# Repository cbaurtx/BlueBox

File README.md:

# BlueBox

BlueBox is a Bluetooth adapter for the RetroBox using an ESP32 system on a chip (ESP32-Wrover).

Refer to the file LICENSE.md for licenses (hardware and software).  

It supports AD2P Bluethooth sources  

Documentation is in the doc directory.

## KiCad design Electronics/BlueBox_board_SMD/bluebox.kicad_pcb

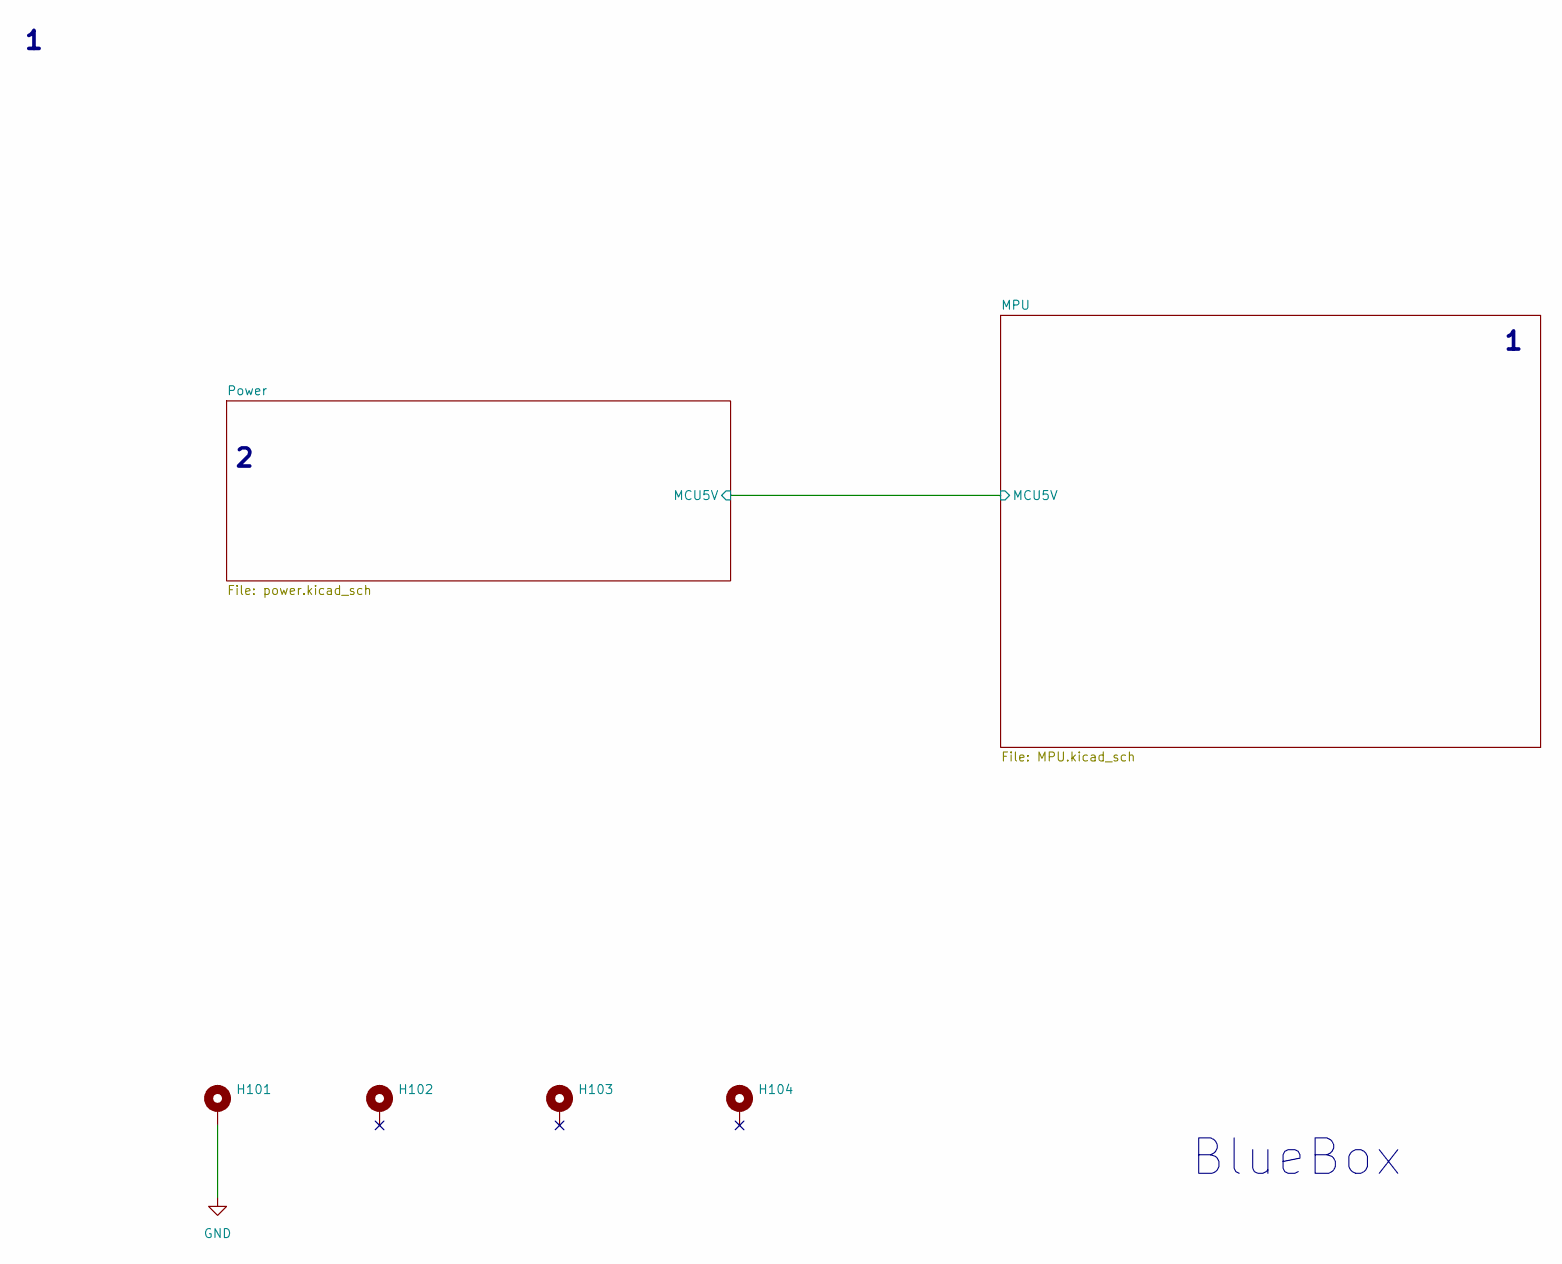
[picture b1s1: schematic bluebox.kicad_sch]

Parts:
H101, H102, H103, H104: MountingHole_Pad; MountingHole_3.2mm_M3_DIN965_Pad

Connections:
GND: H101.1; also elsewhere on the board

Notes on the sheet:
BlueBox

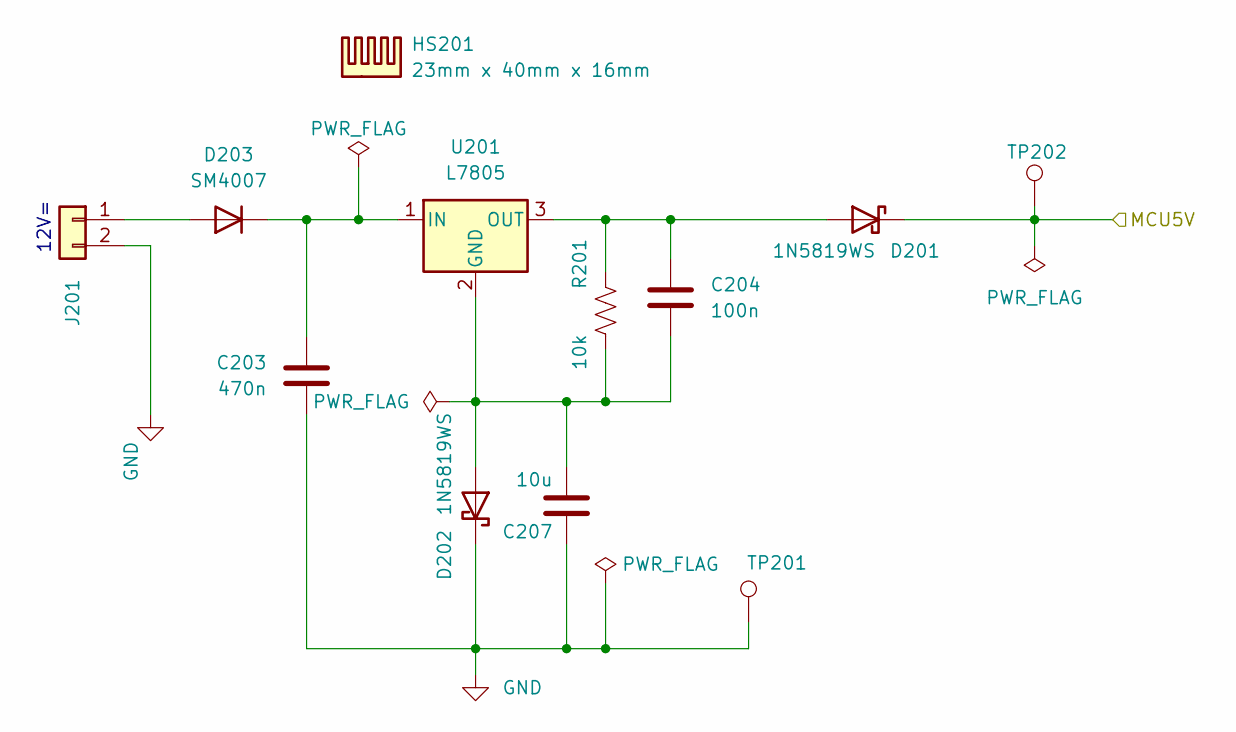
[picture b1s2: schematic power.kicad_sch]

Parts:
C203: 470n; C_0805_2012Metric; LCSC C13967
C204: 100n; C_0603_1608Metric; LCSC C14663
C207: 10u; C_0805_2012Metric; LCSC C15850
D201, D202: 1N5819WS; D_SOD-323; LCSC C191023
D203: SM4007; D_SOD-123F; LCSC C64898
HS201: 23mm x 40mm x 16mm; Heatsink_TO220_23mmX40mm
J201: Conn_01x02; JST_EH_S2B-EH_1x02_P2.50mm_Horizontal
R201: 10k; R_0603_1608Metric; LCSC C25804
TP201, TP202: TestPoint; TestPoint_Loop_D1.80mm_Drill1.0mm_Beaded
U201: L7805; TO-220-3_Horizontal_TabUp

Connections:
/MPU/MCU5V: D201.1 (K), TP202.1; also elsewhere on the board
GND: C203.2, C207.1, D202.1 (K), J201.2, TP201.1; also elsewhere on the board
unnamed: C204.1, D201.2 (A), R201.2, U201.3 (OUT)
unnamed: C204.2, C207.2, D202.2 (A), R201.1, U201.2 (GND)
unnamed: D203.2 (A), J201.1
unnamed: C203.1, D203.1 (K), U201.1 (IN)

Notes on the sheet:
12V=

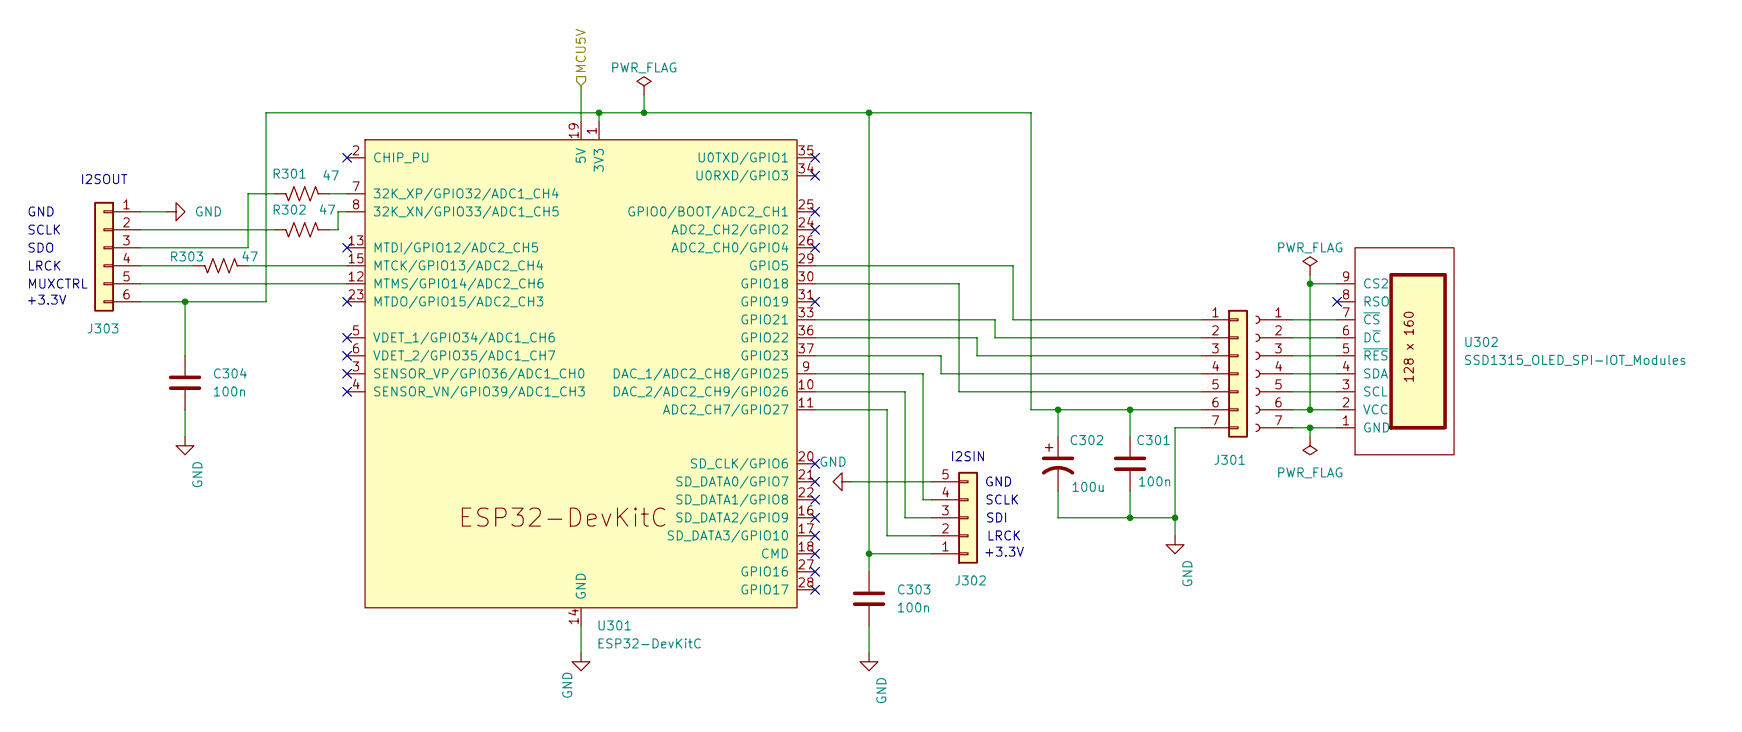
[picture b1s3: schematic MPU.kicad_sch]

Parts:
C301, C303, C304: 100n; C_0603_1608Metric; LCSC C14663
C302: 100u; CP_Radial_D8.0mm_P5.00mm
J301: Conn_01x07; Molex_PicoBlade_53048-0710_1x07_P1.25mm_Horizontal
J302: Conn_01x05; Molex_PicoBlade_53048-0510_1x05_P1.25mm_Horizontal
J303: Conn_01x06; Molex_PicoBlade_53048-0610_1x06_P1.25mm_Horizontal
J399: Conn_01x07_Socket
R301, R302, R303: 47; R_0603_1608Metric; LCSC C23182
U301: ESP32-DevKitC
U302: SSD1315_OLED_SPI-IOT_Modules

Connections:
/MPU/MCU5V: U301.19 (5V); also elsewhere on the board
GND: C301.2, C302.2, C303.2, C304.2, J301.7, J302.5, J303.1, U301.14 (GND), U301.32 (GND), U301.38 (GND); also elsewhere on the board
unnamed: J301.1, U301.29 (GPIO5)
unnamed: J301.2, U301.33 (GPIO21)
unnamed: J301.3, U301.36 (GPIO22)
unnamed: J301.4, U301.37 (GPIO23)
unnamed: J301.5, U301.30 (GPIO18)
unnamed: C301.1, C302.1, C303.1, C304.1, J301.6, J302.1, J303.6, U301.1 (3V3)
unnamed: J302.2, U301.11 (ADC2_CH7/GPIO27)
unnamed: J302.3, U301.10 (DAC_2/ADC2_CH9/GPIO26)
unnamed: J302.4, U301.9 (DAC_1/ADC2_CH8/GPIO25)
unnamed: J303.2, R302.2
unnamed: J303.3, R301.2
unnamed: J303.4, R303.2
unnamed: J303.5, U301.12 (MTMS/GPIO14/ADC2_CH6)
unnamed: J399.1, U302.7 (~CS)
unnamed: J399.2, U302.6 (D~C)
unnamed: J399.3, U302.5 (~RES)
unnamed: J399.4, U302.4 (SDA)
unnamed: J399.5, U302.3 (SCL)
unnamed: J399.6, U302.2 (VCC), U302.9 (CS2)
unnamed: J399.7, U302.1 (GND)
unnamed: R302.1, U301.8 (32K_XN/GPIO33/ADC1_CH5)
unnamed: R301.1, U301.7 (32K_XP/GPIO32/ADC1_CH4)
unnamed: R303.1, U301.15 (MTCK/GPIO13/ADC2_CH4)

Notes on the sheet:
LRCK
SDO
SCLK
I2SIN
SDI
I2SOUT
+3.3V
MUXCTRL
GND

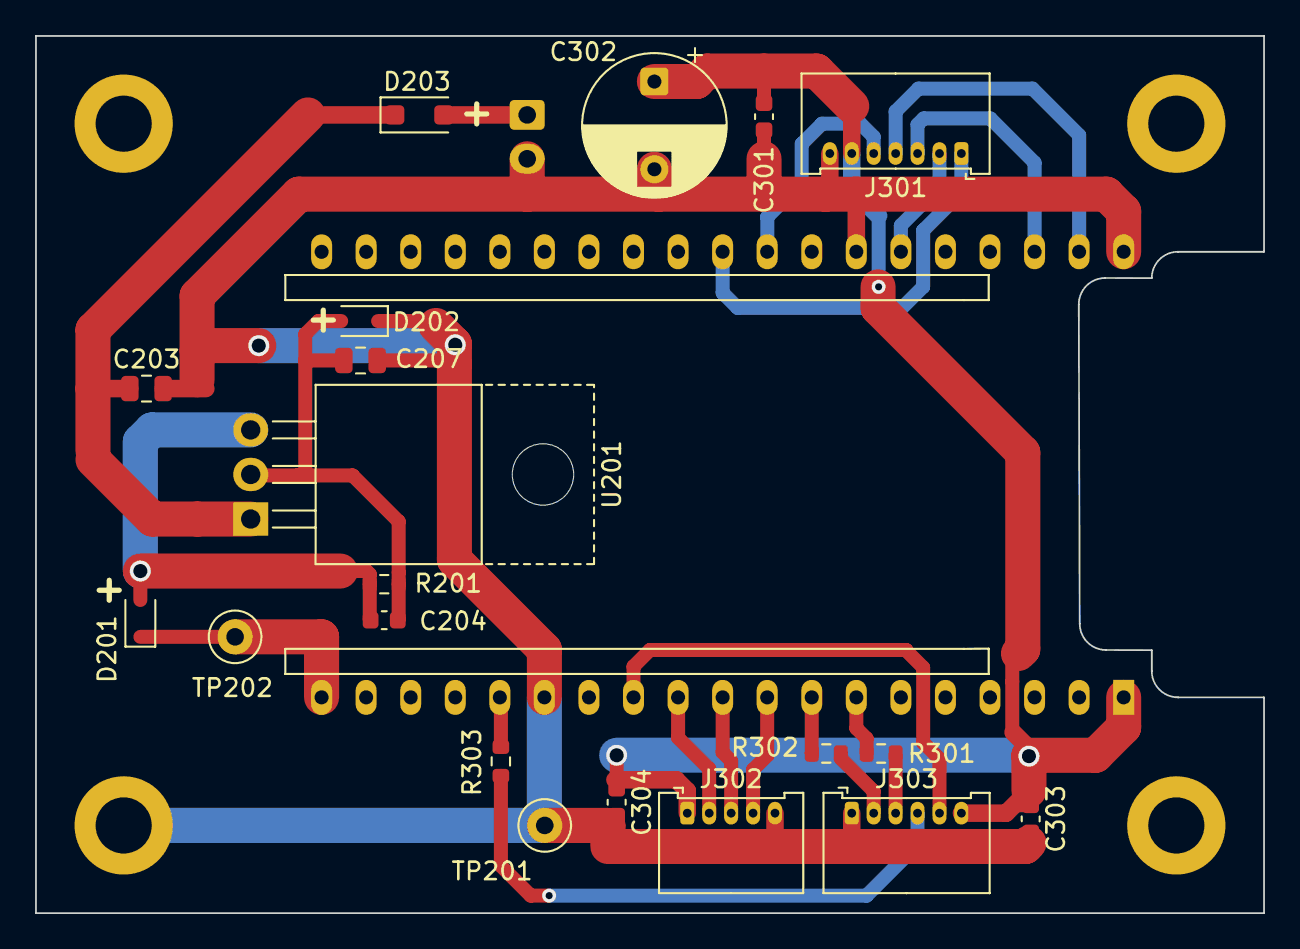
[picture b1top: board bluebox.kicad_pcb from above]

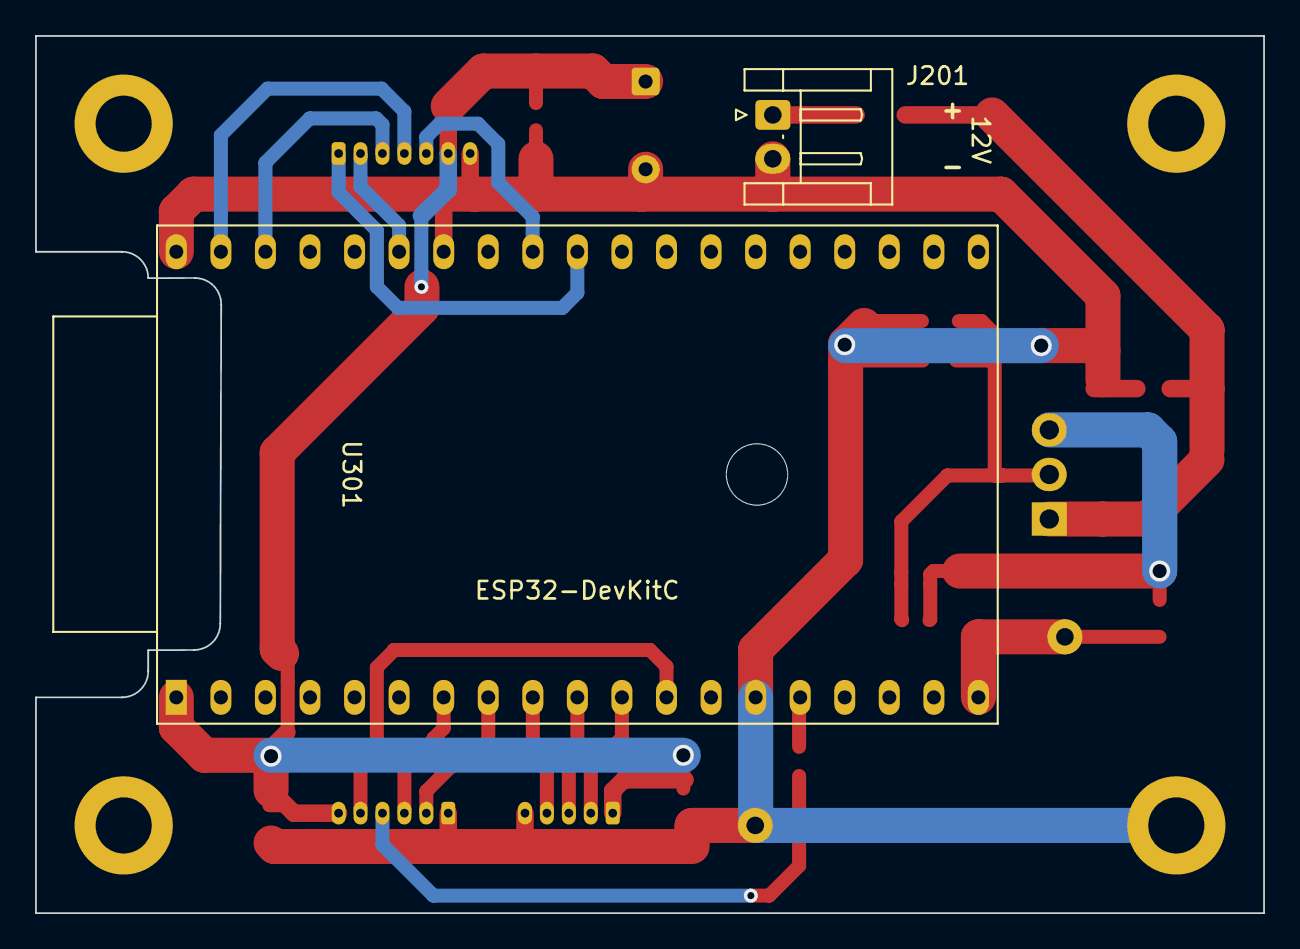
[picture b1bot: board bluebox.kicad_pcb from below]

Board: 2 copper layers, 70.0 x 50.0 mm, 27 parts (2 on the bottom side), 22 nets.

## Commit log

2025-12-27 Initial commit
    Initial Commit
2025-12-27 Added sdkconfig
2026-01-02 Tested also with ESP32 WROOM, changed doc/README.md accordingly
2026-01-02 Corrected typo in doc/README.md
